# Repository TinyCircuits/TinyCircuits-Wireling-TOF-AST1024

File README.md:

# TinyCircuits Wireling TOF
# AST1024 Rev2

The design files are located under design_files/ for the TinyCircuits AST1024 Rev 2 PCB. This is a Wireling board which features the ST VL53L0X IR Time-of-Flight sensor capable of measuring absolute range up to 2m and is most responsive to reflective materials.

Format is in Cadsoft Eagle format - Eagle version 6.2 was used for the original design.

For more infomation on this, check out the product page at TinyCircuits.com

# License:

Design by TinyCircuits.
All design files are released under the Creative Commons Attribution Share-Alike 3.0 License, see the following link for details: http://creativecommons.org/licenses/by-sa/3.0

All text above must be included in any redistribution or derived design

This project uses designs and concepts developed as part of the Arduino project and the LilyPad project.  The TinyCircuits design files themselves (schematics, PCB and libraries) are not directly derived from these works' design files and have been created new, however the concepts and basic architecture behind the TinyDuino and TinyLily products are derived and we thank the hard work of the organizations below for their contributions to open-source hardware:
  
Original Arduino Uno Design by Team Arduino

LilyPad Arduino Design by Leah Buechley and Sparkfun Electronics

Please support the open-source hardware community

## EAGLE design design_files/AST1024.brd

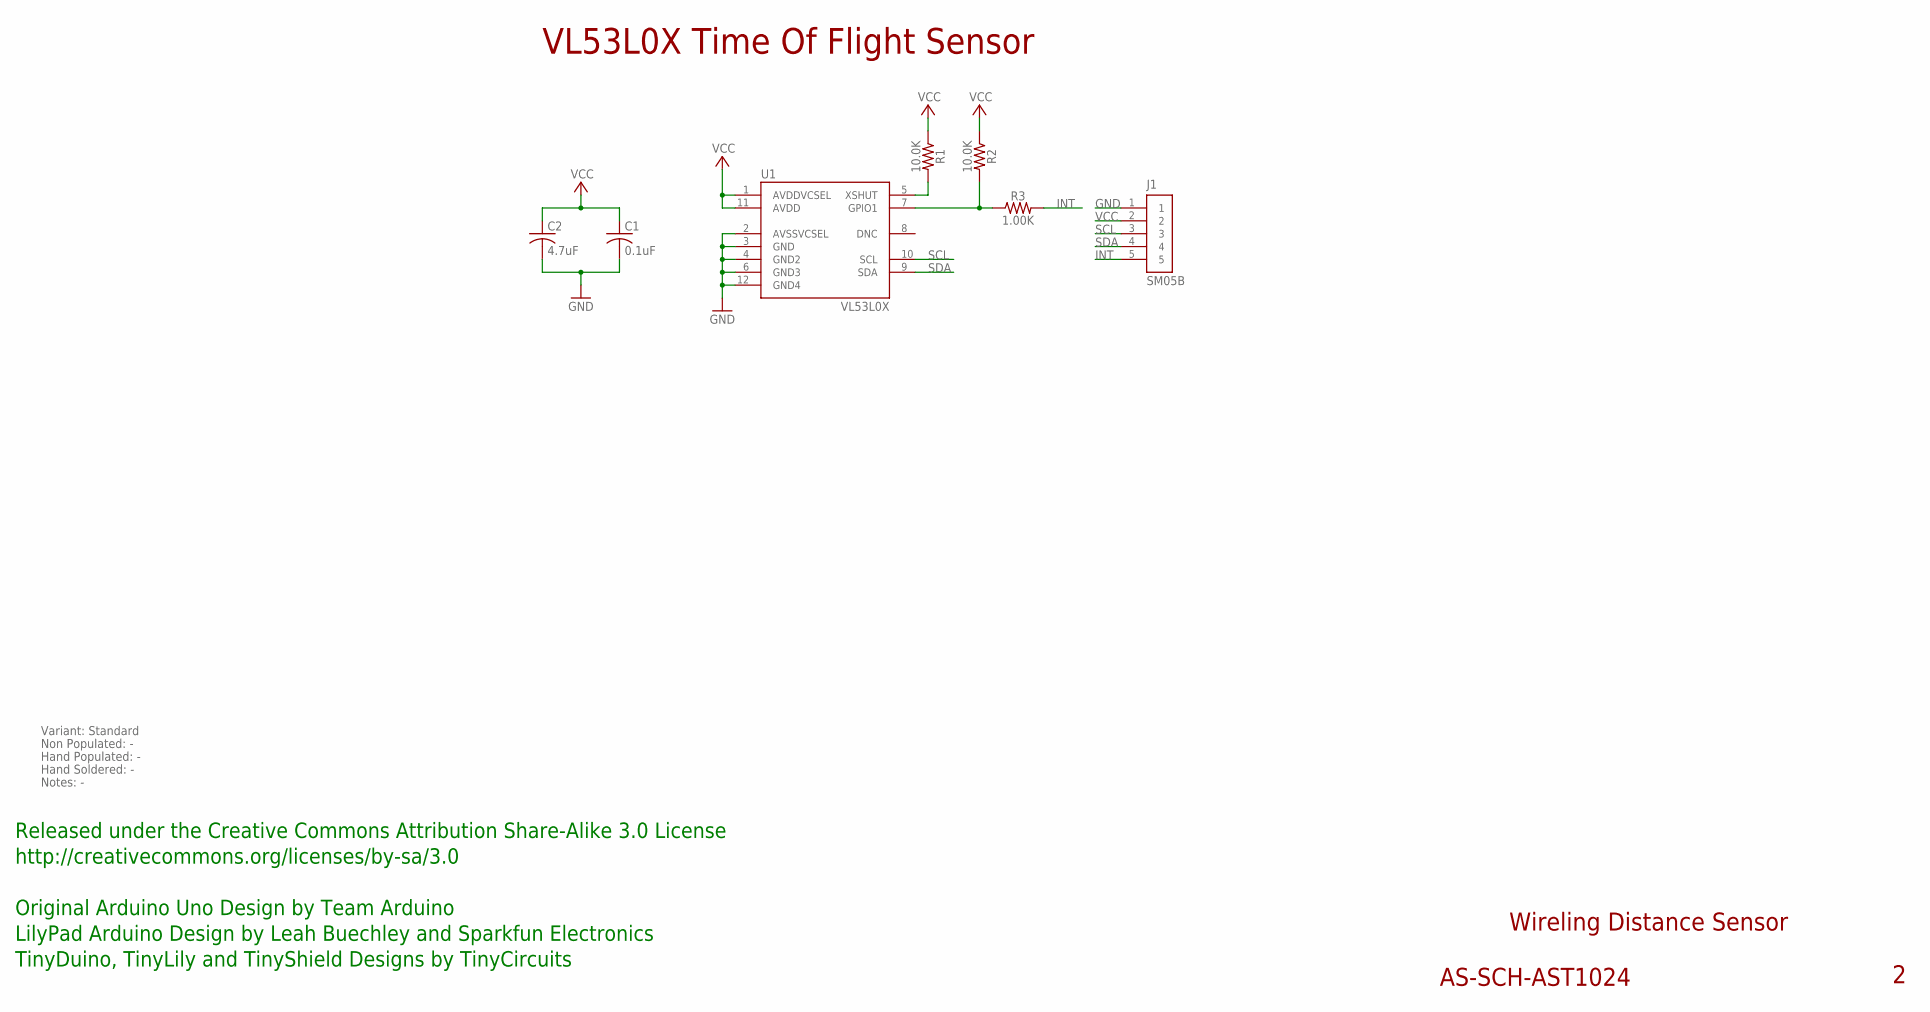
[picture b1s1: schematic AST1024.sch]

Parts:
C1: 0.1uF; C0402
C2: 4.7uF; C0603; PARTNO AS-ITM-00088
J1: SM05B; JST_SH_5X1_EDGE
R1: 10.0K; 0402
R2: 10.0K; 0402; PARTNO AS-ITM-00032
R3: 1.00K; 0402; PARTNO AS-ITM-00003
U1: VL53L0X

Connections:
GND: C1.2, C2.2, J1.1, U1.2 (AVSSVCSEL), U1.3 (GND), U1.4 (GND2), U1.6 (GND3), U1.12 (GND4)
GPIO1: R2.2, R3.1, U1.7 (GPIO1)
INT: J1.5, R3.2
unnamed: R1.2, U1.5 (XSHUT)
SCL: J1.3, U1.10 (SCL)
SDA: J1.4, U1.9 (SDA)
VCC: C1.1, C2.1, J1.2, R1.1, R2.1, U1.1 (AVDDVCSEL), U1.11 (AVDD)

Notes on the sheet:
Wireling Distance Sensor
AS-SCH-AST1024
VL53L0X Time Of Flight Sensor
Released under the Creative Commons Attribution Share-Alike 3.0 License
http://creativecommons.org/licenses/by-sa/3.0
Original Arduino Uno Design by Team Arduino
TinyDuino, TinyLily and TinyShield Designs by TinyCircuits
LilyPad Arduino Design by Leah Buechley and Sparkfun Electronics
Variant: Standard
Non Populated: -
Hand Populated: -
Hand Soldered: -
Notes: -

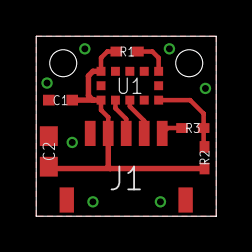
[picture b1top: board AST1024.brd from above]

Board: 2 copper layers, 10.0 x 10.0 mm, 8 parts (0 on the bottom side), 7 nets.

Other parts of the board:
U$1: DOCFIELD-TINYCIRCUITS-PCB

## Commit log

2019-08-05 added datasheet
2019-10-22 update program
2019-12-17 updated documentation
2019-12-18 fix examples
2019-12-18 remove old schem
2019-12-26 added image
2020-01-11 new images
2020-02-04 mass image update
2020-04-16 output picture
2020-08-14 Add CAD data
